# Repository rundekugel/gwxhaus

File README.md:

# gwxhaus
## Greenhouse Controller

*It's just started, not finished.*

Open hardware and firmware to control a greenhouse heating and cooling. Depends on temperature, humidity, wind and time.

An ESP32 controls the motor-controller and reads sensor data.

### Sensors
- Temperature in/out
- Humidity in/out
- Wind
- Soil moisture

There can be a lot of settings depending on sensor values and time.

### Actors
- Motors to open/close the windows
- Valves to control water
- Relais to control heating

The ESP32 is connected via another ESP32, ESP8266 or RaspberryPi to the WWW. Via mqtt the sensor data and actor positions are stored in a database and can be viewd in charts.

Optional, password protected, it's possible to change the settings and manually control the actors.

If any sensor values are out of range, or power fails, there can be messages sent via email, telegram, SMS, telephone (voip), or other channels.

Weather forecast data from Deutscher Wetterdienst https://dwd.api.bund.dev/ can be used to protect windows against storm or hail.

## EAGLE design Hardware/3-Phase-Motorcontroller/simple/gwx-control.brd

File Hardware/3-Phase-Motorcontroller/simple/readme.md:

# gwx-control-motor
## Simple motor controller

Created to control a 3 phase motor to open/close windows of a greenhouse
Created with Eagle Version 7.7

Features:
- switch off motor, if window arrived at end position 
- stop for about 3 seconds, if direction changes, to prevent too high current, which could destroy power switches.

Input: 
- motor on/off
- up/down
- switches for end positions

Output:
- +/- for optocoupler of power motor switcher. Can control DC and AC, 1 to 3 phase motors.
- +/- for direction switch relais

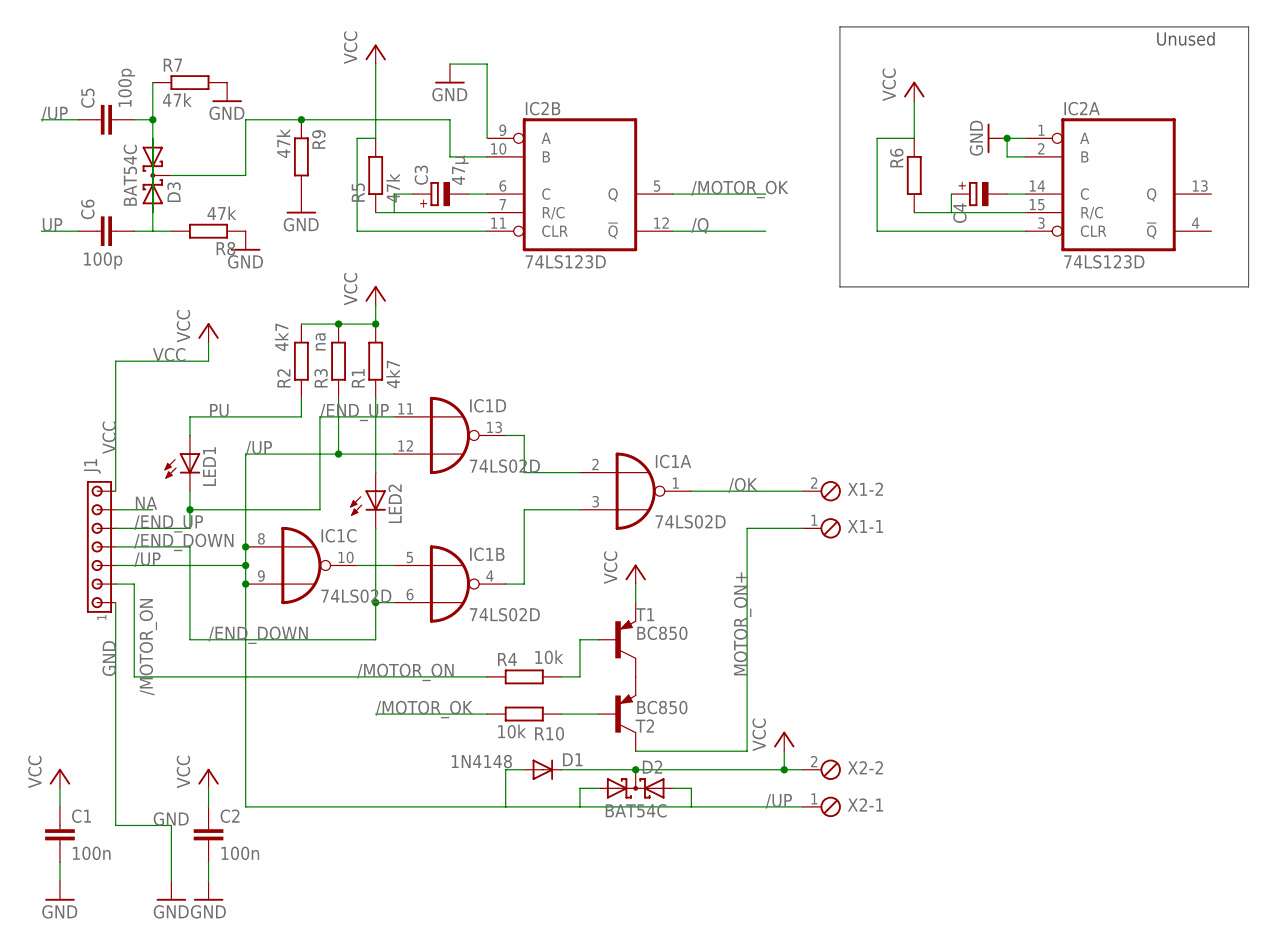
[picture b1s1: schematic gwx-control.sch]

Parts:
C1, C2: 100n; C0603K
C3: 47µ; E5-6
C4: CPOL-EUE5-6; E5-6
C5, C6: 100p; C0603K
D1: 1N4148; DO35-10
D2, D3: BAT54C; SOT23
IC1: 74LS02D; SO14
IC2: 74LS123D; SO16
J1: MTA07-100; 10X07MTA
LED1, LED2: LED_ESML0603; LED_SML0603
R1, R2: 4k7; R0603
R3: na; R0603
R4, R10: 10k; R0603
R5, R7, R8, R9: 47k; R0603
R6: R-EU_R0603; R0603
T1, T2: BC850; SOT23-BEC
X1, X2: MPT2; 2POL254

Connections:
/END_DOWN: IC1.6 (I1), J1.4, LED2.C
/END_UP: IC1.11 (I0), J1.5, LED1.C
/MOTOR_OK: IC2.5 (Q), R10.1
/MOTOR_ON: J1.2, R4.1
/OK: IC1.1 (O), X1.2
/Q: IC2.12 (!Q)
/UP: C5.1, D1.A, D2.1 (A1), D2.2 (A2), IC1.8 (I0), IC1.9 (I1), IC1.12 (I1), J1.3, R3.1, X2.1
GND: C1.2, C2.2, IC1.7 (GND), IC2.1 (A), IC2.2 (B), IC2.8 (GND), IC2.9 (A), J1.1, R7.2, R8.1, R9.2
MOTOR_ON+: T2.C, X1.1
unnamed: C3.+, IC2.7 (R/C), R5.1
unnamed: C3.-, IC2.6 (C)
unnamed: C4.+, IC2.15 (R/C), R6.2
unnamed: C5.2, D3.2 (A2), R7.1
unnamed: IC1.2 (I0), IC1.13 (O)
unnamed: IC1.3 (I1), IC1.4 (O)
unnamed: C6.2, D3.1 (A1), R8.2
unnamed: D3.3 (CC), IC2.10 (B), R9.1
unnamed: C4.-, IC2.14 (C)
unnamed: R10.2, T2.B
unnamed: R4.2, T1.B
unnamed: T1.C, T2.E
unnamed: LED2.A, R1.1
NA: J1.6
PU: LED1.A, R2.1
UP: C6.1, IC1.5 (I0), IC1.10 (O)
VCC: C1.1, C2.1, D1.C, D2.3 (CC), IC1.14 (VCC), IC2.3 (CLR), IC2.11 (CLR), IC2.16 (VCC), J1.7, R1.2, R2.2, R3.2, R5.2, R6.1, T1.E, X2.2

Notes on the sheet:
Unused

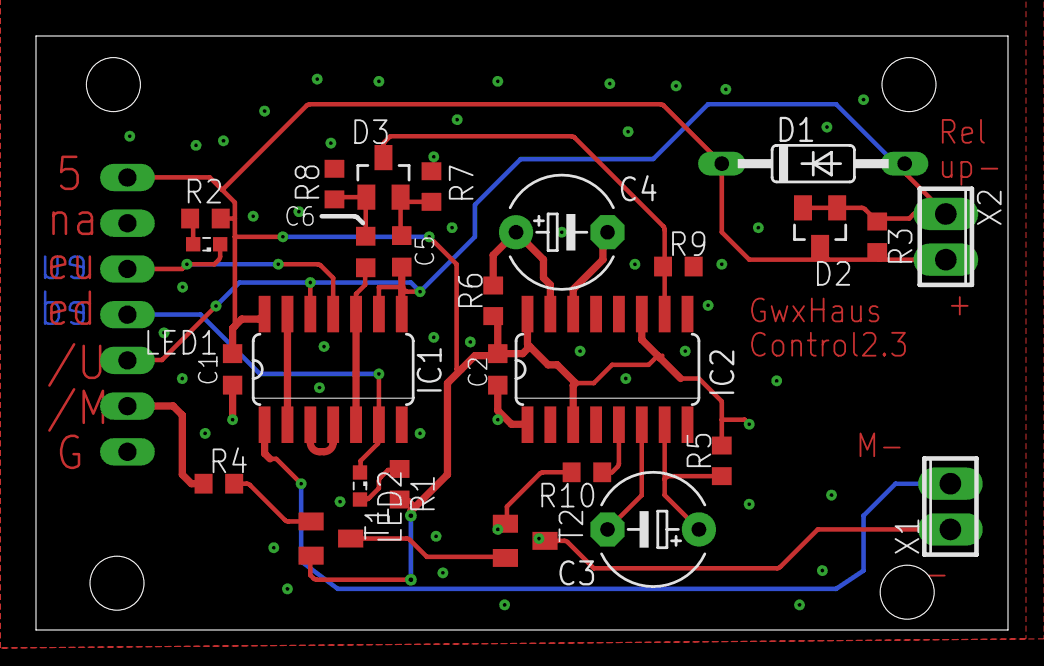
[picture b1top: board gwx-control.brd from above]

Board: 2 copper layers, 54.0 x 33.0 mm, 28 parts (1 on the bottom side), 24 nets.

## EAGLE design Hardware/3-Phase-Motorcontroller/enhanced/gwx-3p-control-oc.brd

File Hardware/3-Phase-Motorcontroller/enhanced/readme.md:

# gwx-control-motor-oc
## Enhanced motor controller

Created to control a 3 phase motor to open/close windows of a greenhouse. 
Created with Eagle Version 7.7

Features:
- switch off motor, if direction changes
- switch off motor, if window arrived at end position 

Input: 
- motor on/off
- up/down
- switches for end positions. Optocoupler protected. 

Output:
- +/- for optocoupler of motorswitcher. Can control DC and AC, 1 to 3 phase motors.
- +/- for direction switch relais.

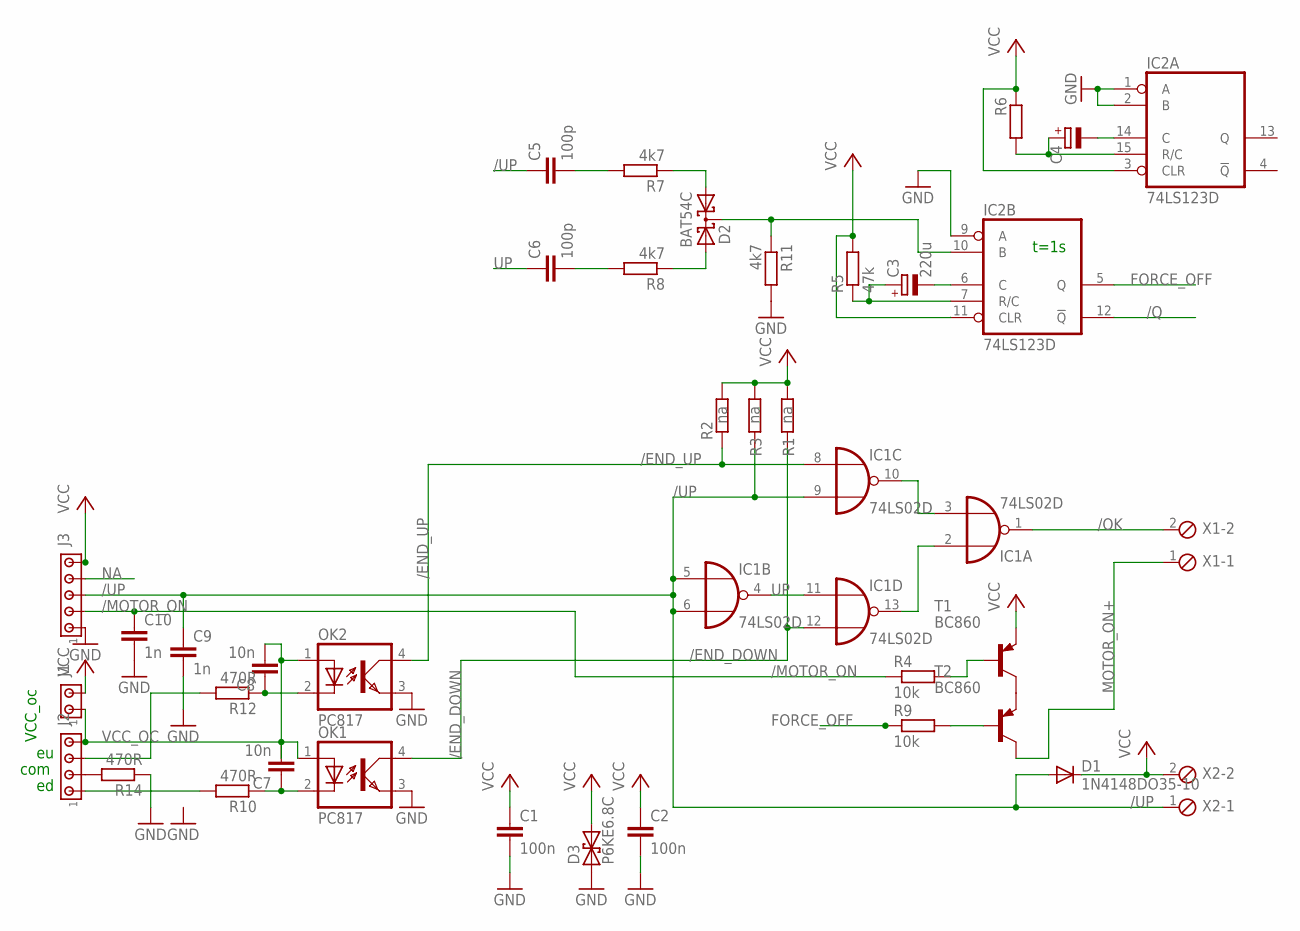
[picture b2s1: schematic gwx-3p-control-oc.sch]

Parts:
C1, C2: 100n; C0603K
C3: 220u; E5-6
C4: CPOL-EUE5-6; E5-6
C5, C6: 100p; C0603K
C7, C8: 10n; C0603
C9, C10: 1n; C0603
D1: 1N4148DO35-10; DO35-10
D2: BAT54C; SOT23
D3: P6KE6.8C; CB417-15
IC1: 74LS02D; SO14
IC2: 74LS123D; SO16
J1: MTA02-100; 10X02MTA
J2: MTA04-100; 10X04MTA
J3: MTA05-100; 10X05MTA
OK1, OK2: PC817; DIL04
R1, R2, R3: na; R0603
R4, R9: 10k; R0603
R5: 47k; R0603
R6: R-EU_R0603; R0603
R7, R8, R11: 4k7; R0603
R10, R12, R14: 470R; R0603
T1, T2: BC860; SOT23-BEC
X1, X2: MPT2; 2POL254

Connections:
/ED: J2.1, R10.2
/END_DOWN: IC1.12 (I1), OK1.4 (COL), R1.1
/END_UP: IC1.8 (I0), OK2.4 (COL), R2.1
/EU: J2.3, R12.2
/MOTOR_ON: C10.1, J3.2, R4.1
/OK: IC1.1 (O), X1.2
/Q: IC2.12 (!Q)
/UP: C5.1, C9.1, D1.A, IC1.5 (I0), IC1.6 (I1), IC1.9 (I1), J3.3, R3.1, X2.1
ECOM: J2.2, R14.2
FORCE_OFF: IC2.5 (Q), R9.1
GND: C1.2, C2.2, C9.2, C10.2, D3.A (1), IC1.7 (GND), IC2.1 (A), IC2.2 (B), IC2.8 (GND), IC2.9 (A), J3.1, OK1.3 (EMIT), OK2.3 (EMIT), R11.2, R14.1
MOTOR_ON+: T2.C, X1.1
unnamed: C3.+, IC2.7 (R/C), R5.1
unnamed: C3.-, IC2.6 (C)
unnamed: C4.+, IC2.15 (R/C), R6.2
unnamed: C5.2, R7.2
unnamed: IC1.3 (I1), IC1.10 (O)
unnamed: IC1.2 (I0), IC1.13 (O)
unnamed: C6.2, R8.2
unnamed: D2.3 (CC), IC2.10 (B), R11.1
unnamed: C4.-, IC2.14 (C)
unnamed: R4.2, T1.B
unnamed: R9.2, T2.B
unnamed: T1.C, T2.E
unnamed: D2.1 (A1), R7.1
unnamed: C7.1, OK1.2 (C), R10.1
unnamed: C8.1, OK2.2 (C), R12.1
unnamed: D2.2 (A2), R8.1
UP: C6.1, IC1.4 (O), IC1.11 (I0)
VCC: C1.1, C2.1, D1.C, D3.C (2), IC1.14 (VCC), IC2.3 (CLR), IC2.11 (CLR), IC2.16 (VCC), J1.2, J3.5, R1.2, R2.2, R3.2, R5.2, R6.1, T1.E, X2.2
VCC_OC: C7.2, C8.2, J1.1, J2.4, OK1.1 (A), OK2.1 (A)

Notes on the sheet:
t=1s
VCC_oc
com

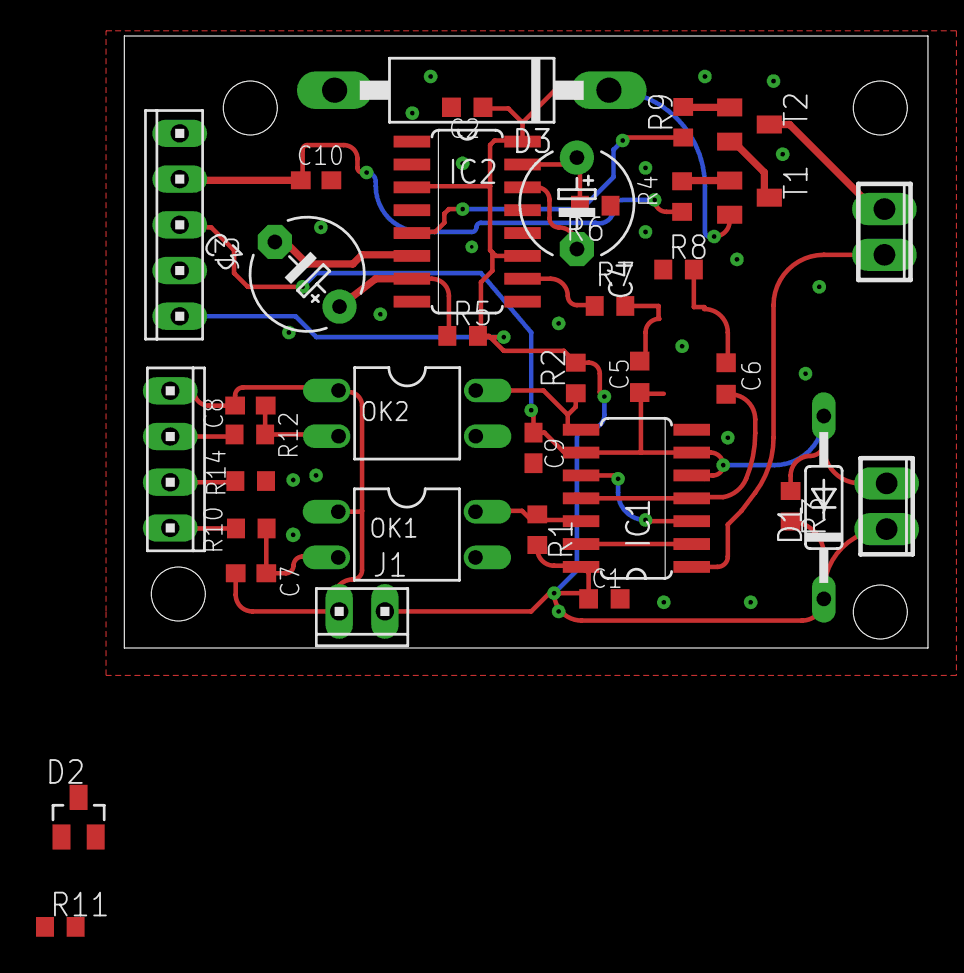
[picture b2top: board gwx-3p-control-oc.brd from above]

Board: 2 copper layers, 44.6 x 34.0 mm, 37 parts (0 on the bottom side), 30 nets.

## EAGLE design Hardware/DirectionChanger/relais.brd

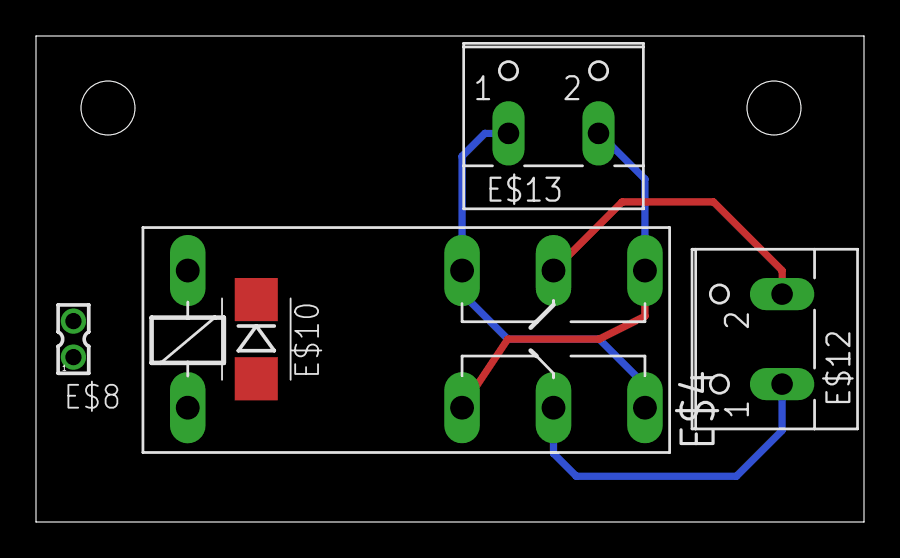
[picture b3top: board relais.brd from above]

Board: 2 copper layers, 46.0 x 27.0 mm, 5 parts (0 on the bottom side), 2 nets.

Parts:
E$4: F4052
E$8: 332-02
E$10: SMB
E$12, E$13: W237-102

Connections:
S$5: E$4.O1, E$4.S2
S$9: E$4.O2, E$4.S1

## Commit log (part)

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2024-04-23 first draft
2024-04-23 added power switch protection
    motor will stop for a few seconds, if direction changes
2024-04-23 doc changed
2024-04-23 more info
2024-04-23 added direction changer brd
2024-05-01 Trigger fixed
2024-05-01 force motor off is now more relyable
    changed from pull down the base of t1 to active switch a 2n T in series
2024-05-01 Changed Motor force off to non inverted mono flop output
2024-05-01 added alternative SMD diode
2024-05-01 pcb size cahnged to 33x54
2024-05-01 LEDs added
2024-05-12 Motor out sign fixed (+)==>(-)
2024-05-13 reading of humidity sensor HYT-221 in µPython
2024-05-13 more doc / mock up
2024-05-13 i2c works now also for ESP32
2024-05-24 Version info added
2024-05-24 HYT221 changed to class, to support multiple sensors
2024-05-24 mocked up
2024-05-25 initial windsensor class for pulse wind sensors
2024-05-25 destructor for irq handler
2024-05-25 simple tcp server
2024-05-25 round values
2024-05-25 prepared for 2 sensors
2024-05-25 prepared seperate files simpleserv and gwxcrlk
2024-05-25 exchanged wifi with uart for core controller
    uart is more stable.
2024-05-25 set/get motor state prepared
2024-05-25 RTC added
2024-05-25 read config added
2024-05-25 cfg is parsed. cfg not case-sensitive, now
    all cfg is overwritten lower case
    getTime() with optional offset for timer
2024-05-26 testmode remote control for HYT221 implemented
2024-05-26 setMotor() parsing fix
2024-05-26 buffer multiple messages
2024-05-26 init pins with 0
2024-05-26 set water timer only, if needed
2024-05-26 fixed quotes
2024-05-26 new cmd: get todos
    new cmd: get todos : "todos?"
    tolerate string in globs.rx for easier todo-construction
2024-05-26 windsensor value can be overwritten for tests
2024-05-26 windsensor pin changed. motor id typo fix.
2024-05-26 typo fix
2024-05-26 option to change verbosity
2024-05-26 hyt221 uses default addr, if addr is None
2024-05-26 HYT221 address can be set per config
2024-05-26 set rtc possible
2024-05-26 cmd "reset!" added
2024-05-27 windsensor param for rounded values
2024-05-27 support deepsleep for ESP32
2024-05-27 Battery Voltage and power supply readable
2024-05-27 ADC calc adjusted to hardware voltage divider
2024-05-27 ligtsleep on power loss, deep sleep on low batt voltage
2024-05-27 parser simplified
2024-05-28 mock up
2024-06-06 init happens in main
2024-06-06 set rtc works with less params
2024-06-09 new pins
2024-06-10 pinning for esp32-light
2024-06-10 degree symbol broke uart data sending
2024-06-30 dose1/2 added
2024-06-30 aes implemented
2024-06-30 crypto-stuff in extra file
2024-06-30 remove secrets before tx
2024-07-01 fix for json compatibility
2024-07-01 sensor data in html table
2024-07-01 less logs
2024-07-01 avoid spamming html page with error messages
2024-07-02 wind speed without thousands of post decimal positions
    and controller temp display although TH-sensor not available
2024-07-02 added km/h to GUI
    don't try to parse Error 504 or empty message
2024-07-04 decryptor moved. i2cscan added.
2024-07-04 mock up
    hyt221 init lean
    docrypt shows version on start
2024-07-07 i2c freq. lower
    try to solve "sensor not found"
2024-07-07 stylesheet and tables added
2024-07-07 Kommentar
2024-07-07 css more green
2024-07-29 modcfg added
2024-07-31 Fix show humidity value for sensor1
2024-07-31 added config of sensor frequency
2024-08-09 table closing row fix
2024-08-09 New: voltage supply monitor for 3 phases
2024-08-13 formatting changed
2024-08-15 watchdog added
2024-08-15 added a voltage calc divider
2024-08-17 using preloaded mqtt msg, now
2024-08-17 mockup
2024-08-17 wind display fix; mockup
2024-08-17 added mqttbuf-service config file
2024-08-17 mqttbuf-service changed for config-file
2024-08-17 more debug features
2024-09-03 new cmd: manually
2024-09-03 disabled unallowed pin
2024-09-04 using parameter filename instead of taskname for the temporary file
2024-09-06 accept some baudrates for comu.init()
2024-09-06 don't show secret config values
2024-09-06 windsensor.init() accept None for diameter
2024-09-06 less verbose
2024-09-06 can set diameter via cfg
2024-09-18 wdt init int fix
2024-09-18 simple login demo added
2024-09-18 motor buttons added
2024-09-18 simple test ==> simple table
2024-09-19 tcp2mqtt.py added
2024-09-19 translator for old fw short key (m1) ==> long (motor1)
2024-09-19 tcp2mqtt config template added
2024-09-19 tcp2mqtt rx-port configurable
2024-09-19 config file can overwrite global vars
2024-09-20 hide buttons, if not authorized
2024-09-20 buttons format
2024-09-21 end switch feature
    calculate a virtual model of window angle by time of motor state on
    windsensor prop fac. added
2024-09-21 checkendswitch py==>uPy
2024-09-21 water keyword Wassern ==> Wn
2024-09-21 added keywords for water 1..4 and virtually window state
2024-09-21 new keywords for states of motor, windows, temp. and humidity
    for motors' and windows' state
2024-09-22 added login and buttons to tec1
2024-09-22 tec1 can display globs and cfg
2024-09-22 switcher can use globs and cfg
2024-09-22 Warnung bei Unterspannung
2024-09-22 windsensor filter changed to windowed sorted filter
2024-09-22 water timetable with 1 minute resolution
2024-09-23 watertables index fix
    + avoid publish SECRET_GLOBS
2024-09-23 set RTC added to tec1
2024-09-23 added keyword RTC to switcher
2024-09-23 rtc added to tcp2mqtt.service
2024-09-23 updated manuell buttons
2024-09-23 neu: sturm warnung
2024-09-23 update config via mqtts
2024-09-23 new parameters: mqtt topic rx/tx
2024-09-23 on too high humidity, close window only, if temperature is < max
2024-09-23 more parameters
    -k=<key> change/add this key
    -d=<data> set data
    -dn=<number> set data as number, without quotes.
    -t=<text> send this text
2024-09-23 deal with wrong value in "globs.verbosity"
2024-09-23 resttime ist humanreadable, now
2024-09-23 zisterne prepared
2024-09-23 water time table configurator
2024-09-23 version inc
2024-09-23 changed str_contains() for php7
2024-09-23 2 tables for demo
2024-09-24 fixed some typos; mockup
2024-09-24 typo fixed
2024-09-25 empty val error fix.val init str/bytes fix
2024-09-26 parse key USB fix for voltage display
2024-10-17 configfile option for updateconfig.py
2024-10-29 updateconfig fix for float values
2024-11-18 html anchors
2024-11-18 tmp file erased
2024-12-23 small fixes
2024-12-26 anleitung
2024-12-26 anleitung added
2024-12-26 manuell state longer duration
2024-12-26 tiny, but powerful design enhancement
2024-12-26 undo deletion of needed tcp2mqtt.py
2024-12-26 switch manually js fix
2024-12-26 with graphic
2025-03-15 added param -js to send config as file
2025-03-15 prepared for more dose
2025-03-21 prevent watchdog from to short intervals
    wdttime default= 90
    minimum= 30
2025-03-21 fixed typo
2025-03-21 readConfig() made failsafe
2025-03-21 avoid crash, if haus-vars missing
2025-03-21 added debug support and new cmd: delcfg
2025-03-28 wifi sockets added
2025-03-29 added more handlers for webpage infos
2025-03-29 one handler to handle multiple nous
2025-03-30 more info for funksteckdosen
2025-03-30 more color for ui
2025-03-30 formating of funkdosenstatus
    tools: byId() ; splitOnce()
    style: beauty up
    tec1: FunkDosenNamen
2025-03-30 motor halb feature prepared
2025-04-05 update blocksize variable
2025-04-05 delete buffer after "modcfg.", even if error
    loop_sleep reduced, we are slow enough.
2025-04-05 prepared for half window position
2025-04-05 doMotors() added to support half position of window
2025-04-05 window close on storm changed
2025-04-05 checkTemp() upgraded to globs.window_pos_dest instead of direct setMotor
2025-04-05 fixed: window goes up if position negative
2025-04-06 motordelay implemented
    if one window at endposition let the other motor run one more second
2025-04-06 motor/fenster cmd can be 0-100 and u,d,h,s
    fenster destination can be:
    (u)p, (d)own, (s)stop, (h)alf.
    or any integer. alowed is only 0-100 !
2025-04-06 tcp2mqtt: param -v for verbosity added
2025-05-02 added schematic as pdf
2025-05-02 gwx-control-simple pcb and sch as pdf added
2025-05-06 Parameter handling changed
2025-05-06 checkWindowPosition_lastTime moved to globs to work also for older python-versions
2025-05-10 watchTimeout added for alert messages if mqtt-LWT
2025-05-10 send alarm only, if not again online after small time
2025-05-10 topics fix
2025-05-10 moved services to new folder server-services
2025-05-31 more features
    + configfile
    + controltopic
    + enable/disable topics
2025-05-31 config modified
    some params stored in watchTimeout.cfg
    only credentials in credentials.dat
2025-05-31 human readable device names
2025-05-31 interval configurable; mockup
2025-05-31 msgdelaytime added to allowed key for config
2025-06-18 more doc
2025-06-18 init dosen. more doc
2025-06-18 timeout watcher for mqtt-LWL added
2025-06-18 changed back to UTF-8
2025-06-18 git revision added to version string
2025-06-20 motor cmd '0' ==> 's'
2025-06-20 USE_END_SWITCHES deactivated, until they are connected
2025-06-20 msg-box deactivated
2025-06-20 setmotor params more compatible: can be : d,u,s,0
2025-06-20 wachTimeout.cfg as default
2025-06-20 more config demo
2025-06-20 prechecked checkbox
2025-06-20 added watertable 3+4
2025-06-20 added: read confg from watertable
2025-06-22 waits added, for direction switch relais.
2025-06-22 uart uses flush, before write
2025-06-24 updateconfig.py works for json-config-files
    json-config files are uploaded, also if no key is given
    gwxcontrol.py: doc updated
2025-06-24 alarm for min. temp added
    comu: ignore, if uart.flush not available
2025-07-13 datetime timezone set to berlin
2025-07-13 fixed cmd receiver
2025-07-13 more feedback for cmds
2025-07-13 versioninfo added to info-cmd
2025-08-04 changed commands from bytearray to string
2025-08-04 added gitignore
2025-08-04 fixed typo time_ms => sleep_ms
2026-02-15 fixed setting timezone
    some servers need additional command: time.tzset()
2026-02-15 updateconfig.cfg as default
2026-04-24 firmware version can be requested
2026-06-04 download watertable
2026-06-04 V0.0.3 json konfig upload/download
2026-06-04 rights check fix
2026-06-04 Mock up: Removed unused code.
2026-06-04 Config transfer button prepared
2026-06-09 kicad files added
2026-06-09 kicad project file
